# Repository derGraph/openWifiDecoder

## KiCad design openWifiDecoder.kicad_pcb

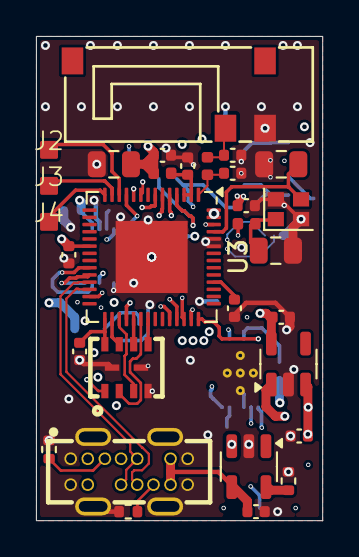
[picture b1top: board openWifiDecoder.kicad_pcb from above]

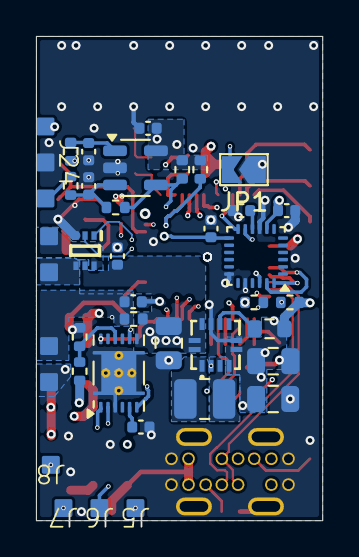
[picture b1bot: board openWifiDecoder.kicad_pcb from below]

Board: 6 copper layers, 15.9 x 26.9 mm, 67 parts (37 on the bottom side), 54 nets.

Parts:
ANT1: PRO-OB-440; ANT-SMD_5P-L13.8-W5.2_PRO-OB-440
BAT1: Battery; SolderPad_1mm_2Pin
C1, C3, C6, C7, C8, C11, C20, C21, C22: .1uF X7R; C_0402_1005Metric
C2: TBC; C_0805_2012Metric
C4, C10, C12, C13, C15, C18, C26: 1uF X7R; C_0402_1005Metric
C5, C17, C19: 10u X7R; C_0805_2012Metric
C9: 470n; C_0402_1005Metric
C14: 680n; C_0402_1005Metric
C16: 10u; C_0805_2012Metric
C23: TBCC; C_0805_2012Metric
C24, C25: C; C_0402_1005Metric
IC1: DRV8212DRLR; SOTFL50P160X60-6N
J1: Motor; SolderPad_1mm_2Pin
J2, J3, J4, J5, J6, J7, J8: Conn_01x01_Pin; SolderPad_1mm_1Pin
J24: Hall; SolderPad_1mm_3Pin
JP1: Download Mode; SolderJumper-2_P1.3mm_Open_TrianglePad1.0x1.5mm_SMALLER
L1: 1.5u 1.5A; L_1008_2520Metric
L2: 2n; L_0402_1005Metric
L3: 24n; L_0402_1005Metric
L4: L; L_0402_1005Metric
R1, R2, R6, R14: 10k; R_0402_1005Metric
R4: 10m 1% 0.07W; R_0402_1005Metric
R5: 1.8M; R_0402_1005Metric
R7: 2k 1%; R_0402_1005Metric
R8: 6k8; R_0402_1005Metric
R9, R10, R11: 5k1; R_0402_1005Metric
R12, R13: 270; R_0402_1005Metric
R15: 100k; R_0603_1608Metric
U1: MIC5317-1.8xM5; SOT-23-5
U2: TPS63051RMWR; QFN-12_L2.5-W2.5-P0.50-TL
U3: ESP32-S3; QFN-56-1EP_7x7mm_P0.4mm_EP4x4mm
U4: ICM-20948; InvenSense_QFN-24_3x3mm_P0.4mm
U5: LTC4054ES5-4.2; TSOT-23-5
U6: TL331; SOT-23-5
U7: BQ27441DRZT-G1A; Texas_S-PDSO-N12
U8: W25Q16JVUUIQ; USON-8_L4.0-W3.0-P0.80-BL_AT25SL321
USB1: MC-802YC-H105; USB-TH_MC-802YC-H105
Y1: 40MHz 10pF; Crystal_SMD_2016-4Pin_2.0x1.6mm

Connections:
+1V8: C4.1, C7.1, U1.5 (VOUT), U4.8 (VDDIO), U4.22 (~CS)
+3V3: C1.1, C3.1, C5.1, C8.2, C13.2, C16.1, C19.1, C20.2, C21.2, J24.1, L2.1, R1.1, R2.1, R10.2, R14.2, R15.1, U1.1 (VIN), U1.3 (EN), U2.4 (VOUT), U2.5 (FB), U3.20 (VDD3P3_RTC), U3.55 (VDDA), U3.56 (VDDA), U4.13 (VDD), U6.5 (V+)
+5V: C12.2, U5.4 (V_{CC}), USB1.A4 (VBUS), USB1.A9 (VBUS), USB1.B4 (VBUS), USB1.B9 (VBUS)
+BATT: C6.2, C17.1, IC1.5 (VM), R4.2, R5.1, U2.10 (ILIM0), U2.11 (EN), U2.12 (VIN), U5.3 (BAT), U7.7 (SRN)
/ESP/GPIO0 Flash Mode: JP1.2 (B), U3.5 (GPIO0)
/ESP/GPIO7: J2.1, U3.12 (GPIO7)
/ESP/GPIO8: J3.1, U3.13 (GPIO8)
/ESP/GPIO9: J4.1, U3.14 (GPIO9)
/ESP/GPIO33: J5.1, U3.38 (GPIO33)
/ESP/GPIO34: J6.1, U3.39 (GPIO34)
/ESP/GPIO35: J7.1, U3.40 (GPIO35)
/ESP/GPIO36: J8.1, U3.41 (GPIO36)
/ESP/RST: R14.1, U3.4 (CHIP_PU)
CLK: U3.33 (SPICLK), U8.6 (CLK)
COMP_DAC: R13.1, U3.6 (GPIO1)
CS: U3.32 (SPICS0), U8.1 (~CS)
D+: U3.26 (GPIO20/USB_D+), USB1.A6 (D+), USB1.B6 (D+)
D-: U3.25 (GPIO19/USB_D-), USB1.A7 (D-), USB1.B7 (D-)
DIG_HALL: R8.2, R10.1, U3.7 (GPIO2), U6.4
FSYNC: U3.27 (GPIO21), U4.11 (FSYNC)
GAUGE_INT: U3.42 (GPIO37), U7.12 (GPOUT)
GND: ANT1.2 (GND), BAT1.1, C1.2, C2.2, C3.2, C4.2, C5.2, C6.1, C7.2, C8.1, C9.1, C10.2, C11.2, C12.1, C13.1, C14.1, C15.2, C16.2, C17.2, C18.2, C19.2, C20.1, C21.1, C22.2, C23.2, C24.2, C25.2, C26.1, IC1.3 (GND), J24.2, JP1.1 (A), R6.2, R7.1, R9.2, R11.2, U1.2 (GND), U2.2 (GND), U2.6 (PFM/PWM), U2.9 (GND), U3.51 (GPIO45), U3.52 (GPIO46), U3.57 (GND), U4.9 (SDO/AD0), U4.18 (GND), U4.20 (GND), U5.2 (GND), U6.2 (V-), U7.3 (V_{SS}), U7.13 (PAD), U8.4 (GND), U8.9 (EP), U8.10 (EP), USB1.1, USB1.2, USB1.3, USB1.4, USB1.A1 (GND), USB1.A12 (GND), USB1.B1 (GND), USB1.B12 (GND), Y1.2, Y1.4
HOLD: U3.30 (SPIHD), U8.7 (IO3)
IMU_INT: U3.11 (GPIO6), U4.12 (INT1)
MPWM1: IC1.1 (IN1), U3.10 (GPIO5)
MPWM2: IC1.2 (IN2), U3.9 (GPIO4)
unnamed: ANT1.1 (FEED), C25.1, L4.2
unnamed: BAT1.2, C10.1, R4.1, U7.6 (BAT), U7.8 (SRP)
unnamed: C2.1, L3.1, Y1.1
unnamed: C26.2, L2.2, U3.2 (VDD3P3), U3.3 (VDD3P3)
unnamed: IC1.6 (OUT1), J1.2
unnamed: IC1.4 (OUT2), J1.1
unnamed: J24.3, R12.2
unnamed: L1.1, U2.1 (L1)
unnamed: L1.2, U2.3 (L2)
unnamed: R15.2, U2.8 (PG)
unnamed: C24.1, L4.1, U3.1 (LNA_IN)
unnamed: C22.1, U3.46 (VDD3P3_CPU)
unnamed: C23.1, U3.53 (XTAL_N), Y1.3
unnamed: L3.2, U3.54 (XTAL_P)
unnamed: C11.1, U4.10 (REGOUT)
unnamed: R7.2, U5.5 (PROG)
unnamed: C14.2, R8.1, R12.1, U6.3 (+)
unnamed: C15.1, R13.2, U6.1 (-)
unnamed: R5.2, R6.1, U7.10 (BIN)
unnamed: C9.2, U7.5 (V_{DD})
unnamed: R9.1, USB1.A5 (CC1)
unnamed: R11.1, USB1.B5 (CC2)
SCL: R2.2, U3.23 (GPIO17), U4.23 (SCL/SCLK), U7.2 (SCL)
SDA: R1.2, U3.24 (GPIO18), U4.24 (SDA/SDI), U7.1 (SDA)
SDI: U3.35 (SPID), U8.5 (DI(IO0))
SDO: U3.34 (SPIQ), U8.2 (DO(IO1))
VDD_SPI: C18.1, U3.29 (VDD_SPI), U8.8 (VCC)
WP: U3.31 (SPIWP), U8.3 (IO2)

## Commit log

2024-11-17 V1.0 Ordered!
2024-11-17 add EN PullUp
2025-03-25 new KiCad version
2025-03-26 change LDO to Buck/Boost Converter in Schematic
2025-03-31 add ESP32 chip + flash antenna missing
2025-04-19 finished Layout, started PCB design agound ESP32
2025-05-13 pcb parts placed not connected
2025-06-02 pcb complete, drc failing 133 Errors
